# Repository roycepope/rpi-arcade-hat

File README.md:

# RPi Recalbox Arcade Control Interface Module
This is a Kicad project of a PCB design for a DIY Arcade system. The goal was to design a PCB that could be easily connected to buttons via JST connectors and the standard Raspberry Pi 40-Pin GPIO header. This is a two layer board with the Top Copper layer being the main signal layer and the bottom board being the ground plane.

## Bill of Materials
| Item         | Qty       |Part Number           |
|--------------|-----------|----------------------|
| JST-XH 4-Pin | 7         |S4B-XH-SM4-TB(LF)(SN) |
| IDT 40-Pin   | 1         |SBH11-PBPC-D20-ST-BK  |

## PCB Render

## RecalBox GPIO Map
```bash
# button control: Y-, Y +, X-, X +, start, select, a, b, tr, y, x, tl
map=1 gpio=pin5,pin3,pin7,pin8,pin15,pin16,pin10,pin11,pin19,pin13,pin12,pin18
map=1,2 gpio=pin24,pin23,pin26,pin29,pin36,pin37,pin31,pin32,pin40,pin35,pin33,pin38
```

|GPIO#  |Pin#       |Control               |  |GPIO#  |Pin#   |Control               |
|-------|-----------|----------------------|--|-------|-------|----------------------|
| 2     | 3         | Player 1 Up          |  |11     | 23    | Player 2 Up          |
| 3     | 5         | Player 1 Down        |  | 8     | 24    | Player 2 Down        |
| 4     | 7         | Player 1 Left        |  | 7     | 26    | Player 2 Left        |
| 14    | 8         | Player 1 Right       |  | 5     | 29    | Player 2 Right       |
| 15    | 10        | Player 1 A           |  | 6     | 31    | Player 2 A           |
| 17    | 11        | Player 1 B           |  | 12    | 32    | Player 2 B           |
| 18    | 12        | Player 1 X           |  | 13    | 33    | Player 2 X           |
| 27    | 13        | Player 1 Y           |  | 19    | 35    | Player 2 Y           |
| 22    | 15        | Player 1 Start       |  | 16    | 36    | Player 2 Start       |
| 23    | 16        | Player 1 Select(Coin)|  | 26    | 37    | Player 2 Select(Coin)|
| 24    | 18        | Player 1 L1          |  | 20    | 38    | Player 2 L1          |
| 10    | 19        | Player 1 R1          |  | 21    | 40    | Player 2 R1          |

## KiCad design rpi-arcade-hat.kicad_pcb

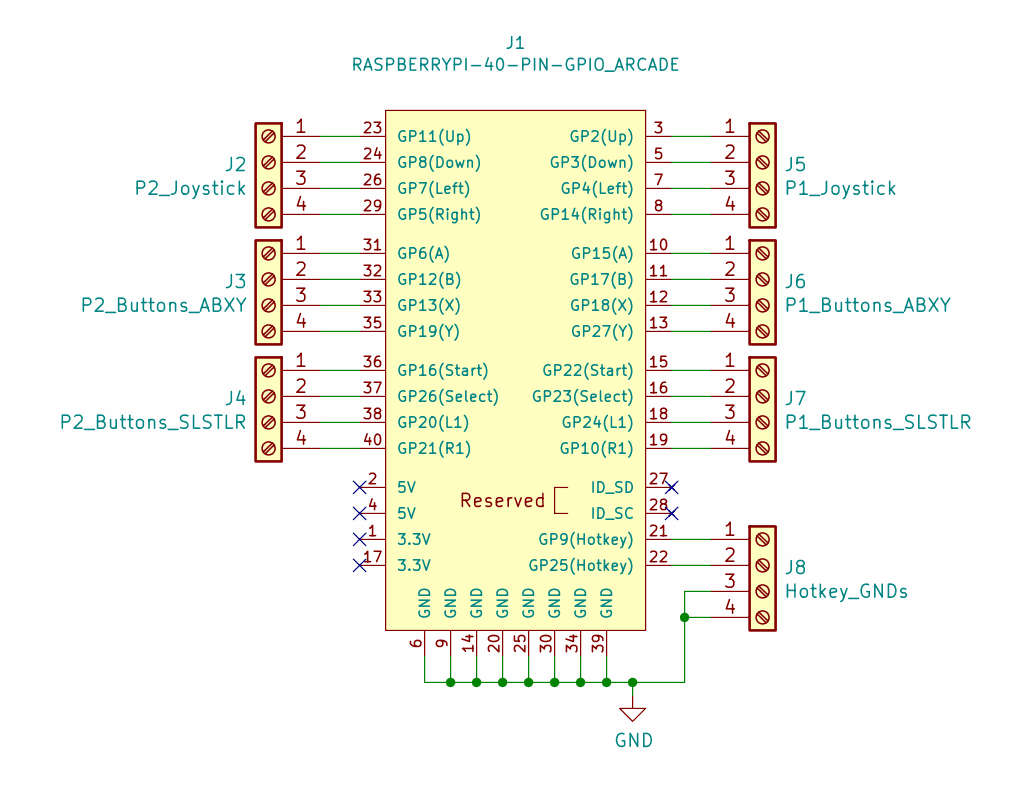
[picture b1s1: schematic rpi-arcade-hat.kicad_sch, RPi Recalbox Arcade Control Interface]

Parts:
J1: RASPBERRYPI-40-PIN-GPIO_ARCADE; IDC-Header_2x20_P2.54mm_Vertical
J2: P2_Joystick; JST_XH_B4B-XH-A_1x04_P2.50mm_Vertical
J3: P2_Buttons_ABXY; JST_XH_B4B-XH-A_1x04_P2.50mm_Vertical
J4: P2_Buttons_SLSTLR; JST_XH_B4B-XH-A_1x04_P2.50mm_Vertical
J5: P1_Joystick; JST_XH_B4B-XH-A_1x04_P2.50mm_Vertical
J6: P1_Buttons_ABXY; JST_XH_B4B-XH-A_1x04_P2.50mm_Vertical
J7: P1_Buttons_SLSTLR; JST_XH_B4B-XH-A_1x04_P2.50mm_Vertical
J8: Hotkey_GNDs; JST_XH_B4B-XH-A_1x04_P2.50mm_Vertical

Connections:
GND: J1.6 (GND), J1.9 (GND), J1.14 (GND), J1.20 (GND), J1.25 (GND), J1.30 (GND), J1.34 (GND), J1.39 (GND), J8.3, J8.4
unnamed: J1.3 (GP2(Up)), J5.1
unnamed: J1.5 (GP3(Down)), J5.2
unnamed: J1.7 (GP4(Left)), J5.3
unnamed: J1.8 (GP14(Right)), J5.4
unnamed: J1.10 (GP15(A)), J6.1
unnamed: J1.11 (GP17(B)), J6.2
unnamed: J1.12 (GP18(X)), J6.3
unnamed: J1.13 (GP27(Y)), J6.4
unnamed: J1.15 (GP22(Start)), J7.1
unnamed: J1.16 (GP23(Select)), J7.2
unnamed: J1.18 (GP24(L1)), J7.3
unnamed: J1.19 (GP10(R1)), J7.4
unnamed: J1.21 (GP9(Hotkey)), J8.1
unnamed: J1.22 (GP25(Hotkey)), J8.2
unnamed: J1.23 (GP11(Up)), J2.1
unnamed: J1.24 (GP8(Down)), J2.2
unnamed: J1.26 (GP7(Left)), J2.3
unnamed: J1.29 (GP5(Right)), J2.4
unnamed: J1.31 (GP6(A)), J3.1
unnamed: J1.32 (GP12(B)), J3.2
unnamed: J1.33 (GP13(X)), J3.3
unnamed: J1.35 (GP19(Y)), J3.4
unnamed: J1.36 (GP16(Start)), J4.1
unnamed: J1.37 (GP26(Select)), J4.2
unnamed: J1.38 (GP20(L1)), J4.3
unnamed: J1.40 (GP21(R1)), J4.4

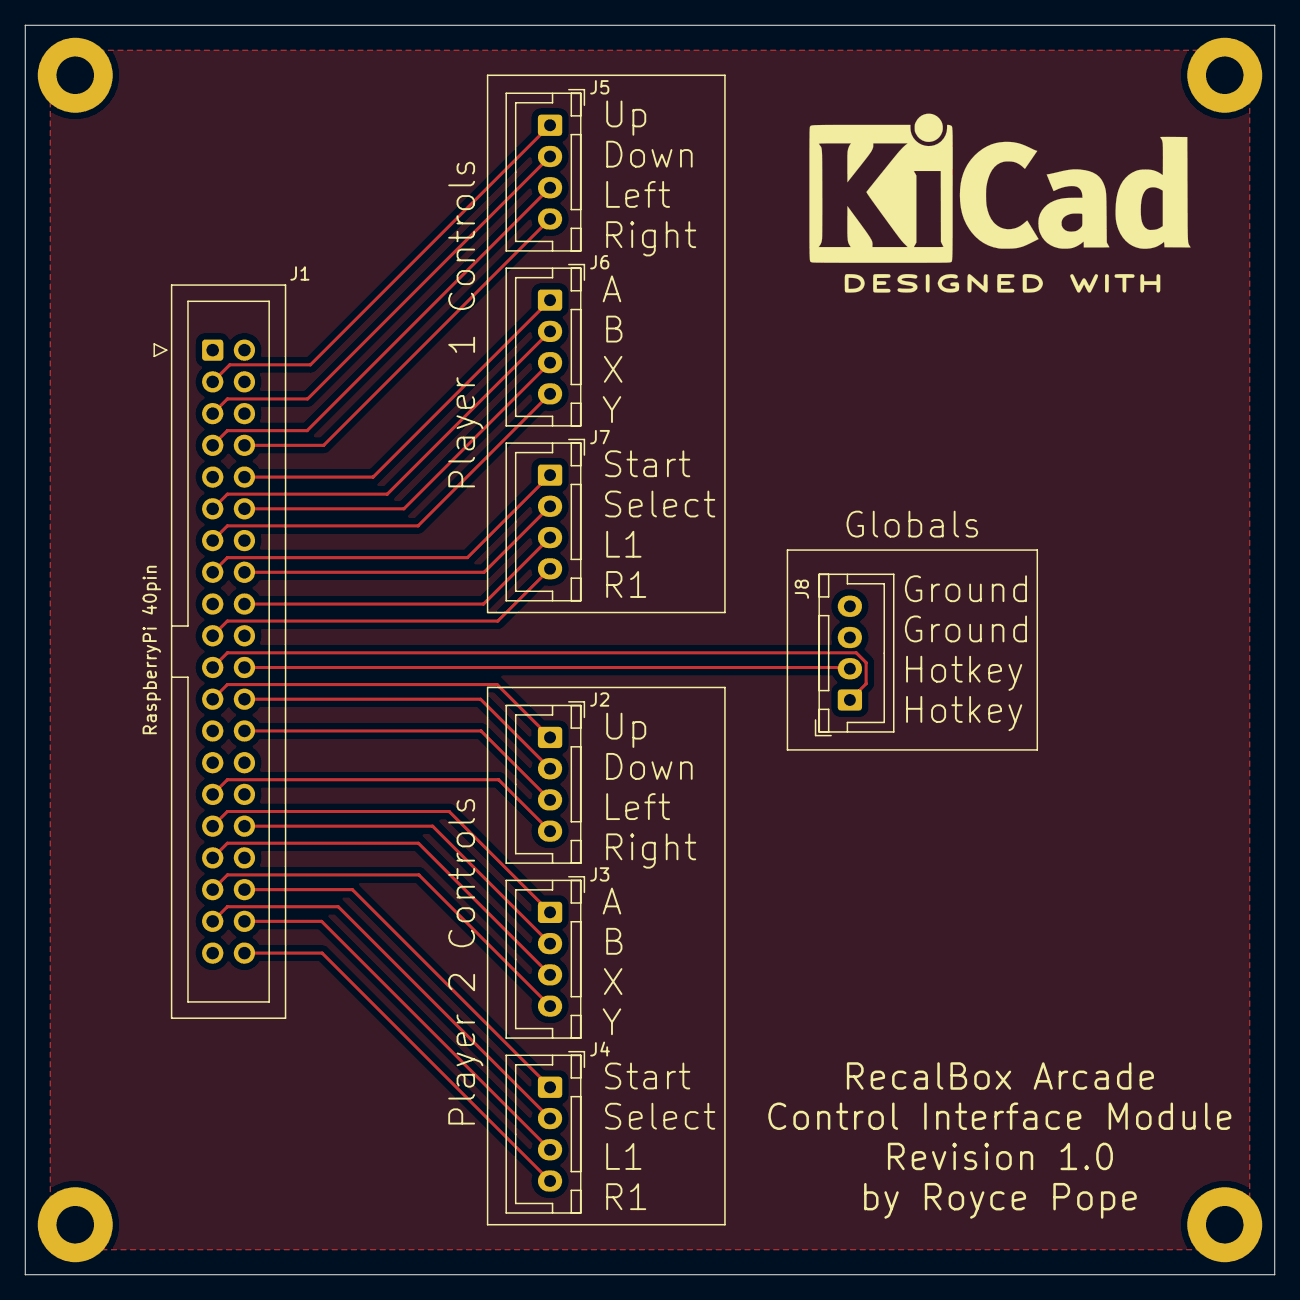
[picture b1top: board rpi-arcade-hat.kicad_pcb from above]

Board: 2 copper layers, 100.0 x 100.0 mm, 8 parts (0 on the bottom side), 27 nets.

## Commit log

2021-09-26 Initial commit of the RPi Recalbox Arcade Control Interface Module KiCad project files
2021-09-26 Added 100mm PCBWay layout
2021-09-27 Update PCB render
2021-09-27 Added description and BOM
2021-09-27 Revert "Update README.md"
    This reverts commit 3ef2cac192711f4e6be95e38b9a516649c1dacb2.
2021-09-29 Add Part numbers, modify silkscreen, remove unused layers.
2021-09-29 Add GPIO and Pin mapping to README
2022-03-26 Update to KiCad 6.0
    There are new file extensions for KiCad 6.0. I left the old files for backwards compatibility.
2023-01-12 Formatting..
